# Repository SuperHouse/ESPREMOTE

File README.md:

ESPREMOTE: ESP8266 Remote Control Adapter
=========================================

Copyright 2017-2018 SuperHouse Automation Pty Ltd  www.superhouse.tv  

Allows an RF remote control to be connected to an ESP8266 so that it
can be triggered remotely as if the buttons were pushed.

Features:

 * ESP8266 MCU with wifi.
 * 4 low-side switched transistor outputs.
 * Headers for GND and 3.3V to power the remote control.
 * 2.1mm DC jack for 5-24Vdc power input.
 * Efficient 3.3V switchmode power supply.

Note: Images below are for old v1.0 release. Images need updating.

More information is available at:

  http://www.superhouse.tv/espremote

INSTALLATION
------------
The design is saved as an EAGLE project. EAGLE PCB design software is
available from www.cadsoftusa.com free for non-commercial use. To use
this project download it and place the directory containing these files
into the "eagle" directory on your computer.

DISTRIBUTION
------------
The specific terms of distribution of this project are governed by the
license referenced below.

LICENSE
-------
Licensed under the TAPR Open Hardware License (www.tapr.org/OHL).
The "license" folder within this repository also contains a copy of
this license in plain text format.

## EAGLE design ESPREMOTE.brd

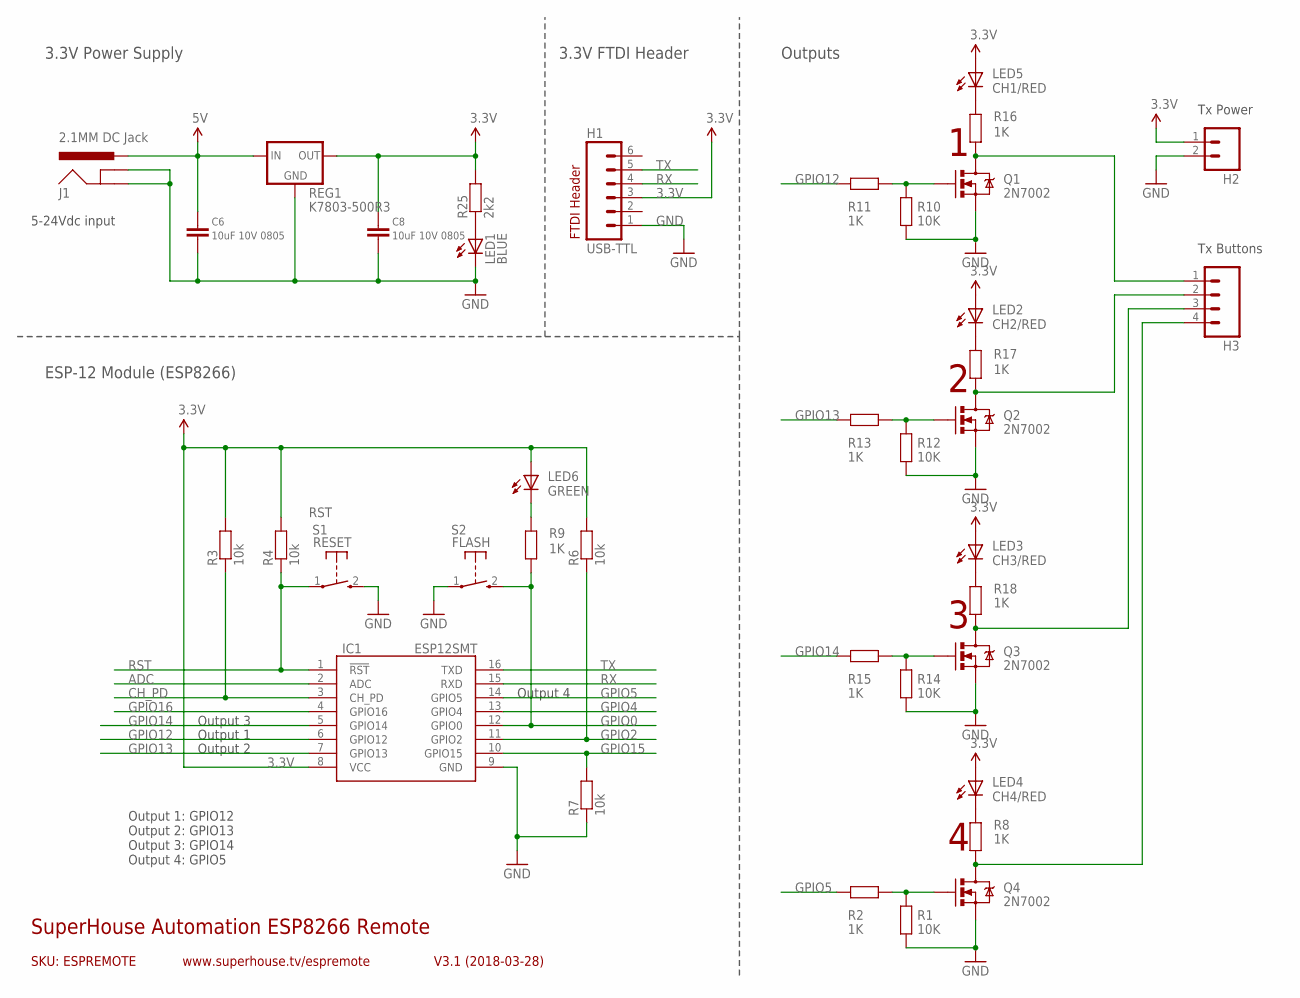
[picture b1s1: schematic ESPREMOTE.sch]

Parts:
C6, C8: 10uF 10V 0805; C0805
H1: USB-TTL; 1X06
H2: M02PTH; 1X02
H3: M04PTH; 1X04
IC1: ESP12SMT; ESP12
J1: 2.1MM DC Jack; POWER_JACK_PTH_SLOTS
LED1: BLUE; LED-0603
LED2: CH2/RED; LED-0603
LED3: CH3/RED; LED-0603
LED4: CH4/RED; LED-0603
LED5: CH1/RED; LED-0603
LED6: GREEN; LED-0603
Q1, Q2, Q3, Q4: 2N7002; SOT23-3
R1, R10, R12, R14: 10K; 0603
R2, R8, R9, R11, R13, R15, R16, R17, R18: 1K; 0603
R3, R4, R6, R7: 10k; 0603
R25: 2k2; 0603
REG1: K7803-500R3; K78XX-500R3
S1: RESET; TACTILE_SWITCH_SMD_2PIN_TINY
S2: FLASH; TACTILE_SWITCH_SMD_2PIN_TINY

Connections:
3.3V: C8.1, H1.3, H2.1, IC1.8 (VCC), LED2.A, LED3.A, LED4.A, LED5.A, LED6.A, R3.2, R4.2, R6.2, R25.2, REG1.3 (OUT)
5V: C6.1, J1.PWR, REG1.1 (IN)
ADC: IC1.2 (ADC)
CH_PD: IC1.3 (CH_PD), R3.1
GND: C6.2, C8.2, H1.1, H2.2, IC1.9 (GND), J1.GND, J1.GNDBREAK, LED1.C, Q1.2 (S), Q2.2 (S), Q3.2 (S), Q4.2 (S), R1.1, R7.1, R10.1, R12.1, R14.1, REG1.2 (GND), S1.2 (S), S2.1
GPIO0: IC1.12 (GPIO0), R9.2, S2.2 (S)
GPIO2: IC1.11 (GPIO2), R6.1
GPIO4: IC1.13 (GPIO4)
GPIO5: IC1.14 (GPIO5), R2.2
GPIO12: IC1.6 (GPIO12), R11.2
GPIO13: IC1.7 (GPIO13), R13.2
GPIO14: IC1.5 (GPIO14), R15.2
GPIO15: IC1.10 (GPIO15), R7.2
GPIO16: IC1.4 (GPIO16)
unnamed: Q1.1 (G), R10.2, R11.1
unnamed: Q2.1 (G), R12.2, R13.1
unnamed: H3.2, Q2.3 (D), R17.2
unnamed: LED3.C, R18.1
unnamed: H3.1, Q1.3 (D), R16.2
unnamed: H3.4, Q4.3 (D), R8.2
unnamed: Q4.1 (G), R1.2, R2.1
unnamed: H3.3, Q3.3 (D), R18.2
unnamed: Q3.1 (G), R14.2, R15.1
unnamed: LED4.C, R8.1
unnamed: LED2.C, R17.1
unnamed: LED1.A, R25.1
unnamed: LED5.C, R16.1
unnamed: LED6.C, R9.1
RST: IC1.1 (!RST), R4.1, S1.1
RX: H1.4, IC1.15 (RXD)
TX: H1.5, IC1.16 (TXD)

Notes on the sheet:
SKU: ESPREMOTE
SuperHouse Automation ESP8266 Remote
V3.1 (2018-03-28)
www.superhouse.tv/espremote
3.3V Power Supply
FTDI Header
Outputs
ESP-12 Module (ESP8266)
3.3V FTDI Header
5-24Vdc input
Output 1: GPIO12 Output 2: GPIO13 Output 3: GPIO14 Output 4: GPIO5
Output 1
Output 2
Output 3
Output 4
Tx Power
Tx Buttons

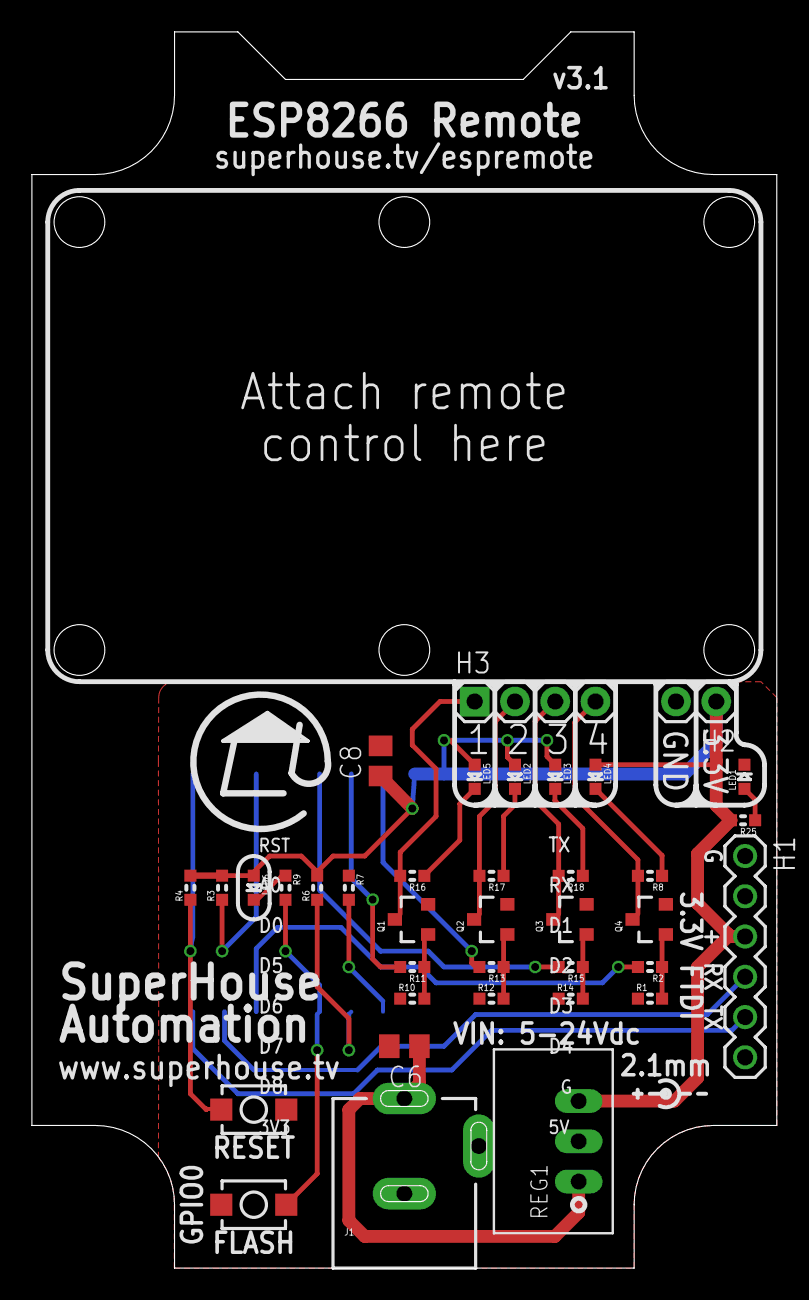
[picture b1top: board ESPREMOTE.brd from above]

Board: 2 copper layers, 47.0 x 78.0 mm, 38 parts (1 on the bottom side), 28 nets.

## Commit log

2017-06-01 Initial project import after schematic and board layout
2017-07-05 Finished schematic and routing for v1.0 release
2017-07-05 Added images and README
2017-07-29 Final silkscreen and label improvements for v1.0 release
2017-07-29 Added output info to silkscreen
2017-07-29 Changed output 4 from GPIO16 to GPIO4
2017-07-30 Replaced 2.1mm DC jack and switchmode reg with USB socket and linear reg
2018-03-09 Replaced crappy SMPS with linear reg and micro USB socket
2018-03-09 Replaced USB socket and linear reg with 2.1mm DC jack and SMPS module
2018-03-09 Updated README for v3.0
2018-03-09 Improved labels for v3.0 release
2018-03-28 Fixed ESP12 pinout for v3.1 release

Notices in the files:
ESPREMOTE.brd:
(C)2017 SuperHouse
Hardware Licence: tapr.org/ohl
parts and their libraries:
freetronics-original: Licensing: CC v3.0 Share-Alike You are welcome to use this library for commercial purposes.
